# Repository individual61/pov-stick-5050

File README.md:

# POV-Stick

POV Stick 5050: A persistence of vision stick with 10 APA102C RGB LEDs, one button, and a surprise.

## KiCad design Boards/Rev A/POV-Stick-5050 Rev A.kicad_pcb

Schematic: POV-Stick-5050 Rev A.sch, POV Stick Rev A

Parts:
C1, C3: 0.1uF; C_0603_HandSoldering; Voltage Rating 50V; MFR P/N 06035C104KAZ2A
C2: 100uF; CP_Tantalum_Case-C_EIA-6032-28_Reflow; Voltage Rating 10V; MFR P/N TAJC107K010RNJ
C4: 10uF; C_0805_HandSoldering; Voltage Rating 16V; MFR P/N GRM21BR61C106KE15L
D1: Heartbeat LED; LED_0603_HandSoldering; MFR P/N LS L29K-G1J2-1-Z
J1: ISP_Header; ISP_Header_Pogo_2x03_Pitch2.54mm
J2: Batt Conn; JST_PH_S2B-PH-K_02x2.00mm_Angled; Part Number S2B-PH-K-S
R1: 4.7k; R_0603_HandSoldering; MFR P/N CR0603-FX-4701ELF
R2: 10k; R_0603_HandSoldering; MFR P/N RC0603FR-0710KL
R3: 1.5k; R_0603_HandSoldering; MFR P/N RC0603FR-071K5L
S1: Button; SW_TH_Tactile_Omron_B3F-10xx; Part Number B3F-1000
SW1: Power Switch; E-Switch_EG1390; Part Number AYZ0202AGRLC
U1: ATTINY85-20SU; SOIC-8_3.9x4.9mm_Pitch1.27mm
U2, U3, U4, U5, U6, U7, U8, U9, U10, U11: APA102C; LED_RGB_5050-6_Compact

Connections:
+BATT: C2.1, C3.1, C4.1, J1.2, R1.1, R2.1, SW1.2, SW1.5, U1.8 (VCC), U2.4, U3.4, U4.4, U5.4, U6.4, U7.4, U8.4, U9.4, U10.4, U11.4
/MOSI/WS2812Data: J1.4, U1.5 (PB0(MOSI/DI/SDA/AIN0/OC0A/~OC1A~/AREF/P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), U2.1
/PIN3/SW3: R2.2, S1.1, S1.2, U1.3 (PB4(XTAL2/CLKO/OC1B/ADC2/PCINT4))
/PIN6/SCK: J1.1, U1.6 (PB1(MISO/DO/AIN1/OC0B/OC1A/PCINT1))
/SCK/WS2812Clock: J1.3, U1.7 (PB2(SCK/USCK/SCL/T0/INT0/ADC1/PCINT2)), U2.2
GND: C1.2, C2.2, C3.2, C4.2, J1.6, J2.2, R3.2, S1.3, S1.4, U1.4 (GND), U2.3, U3.3, U4.3, U5.3, U6.3, U7.3, U8.3, U9.3, U10.3, U11.3
unnamed: C1.1, J1.5, R1.2, U1.1 (PB5(~RESET~/dW/ADC0/PCINT5))
unnamed: D1.1, R3.1
unnamed: D1.2, U1.2 (PB3(XTAL1/CLKI/~OC1B~/ADC3/PCINT3))
unnamed: J2.1, SW1.1, SW1.4
unnamed: U2.5, U3.2
unnamed: U2.6, U3.1
unnamed: U3.5, U4.2
unnamed: U3.6, U4.1
unnamed: U4.5, U5.2
unnamed: U4.6, U5.1
unnamed: U5.5, U6.2
unnamed: U5.6, U6.1
unnamed: U6.5, U7.2
unnamed: U6.6, U7.1
unnamed: U7.5, U8.2
unnamed: U7.6, U8.1
unnamed: U8.5, U9.2
unnamed: U8.6, U9.1
unnamed: U9.6, U10.1
unnamed: U9.5, U10.2
unnamed: U10.5, U11.2
unnamed: U10.6, U11.1

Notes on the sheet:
NOTE: TURN SWITCH OFF TO PROGRAM WITH ISP
ATTINY85 SOIC-8
Vf = 1.8V, 2 mA Ityp 5V-1.8 = 3.2V 3.2V/1.5k = 2.1 mA

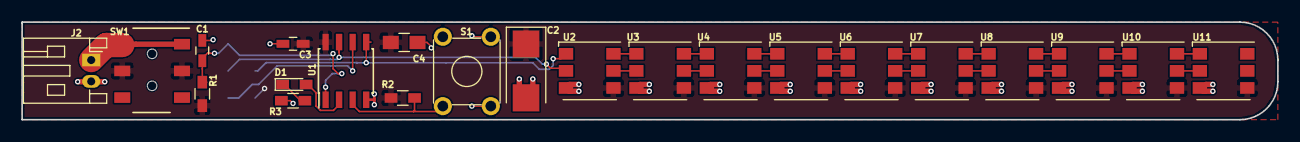
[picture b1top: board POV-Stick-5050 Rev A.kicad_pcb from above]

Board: 2 copper layers, 117.7 x 9.1 mm, 23 parts (1 on the bottom side), 28 nets.

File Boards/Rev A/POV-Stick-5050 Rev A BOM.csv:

"Id";"Designator";"Package";"Quantity";"Designation";"Supplier and ref";
1;"U1";"SOIC-8_3.9x4.9mm_Pitch1.27mm";1;"ATTINY85-20SU";;;
2;"C1,C3";"C_0603_HandSoldering";2;"0.1uF";;;
3;"C4";"C_0805_HandSoldering";1;"10uF";;;
4;"D1";"LED_0603_HandSoldering";1;"Heartbeat LED";;;
5;"J2";"JST_PH_S2B-PH-K_02x2.00mm_Angled";1;"Batt Conn";;;
6;"R1";"R_0603_HandSoldering";1;"4.7k";;;
7;"R2";"R_0603_HandSoldering";1;"10k";;;
8;"R3";"R_0603_HandSoldering";1;"1.5k";;;
9;"S1";"SW_TH_Tactile_Omron_B3F-10xx";1;"Button";;;
10;"SW1";"E-Switch_EG1390";1;"Power Switch";;;
11;"U2,U3,U4,U5,U6,U7,U8,U9,U10,U11";"LED_RGB_5050-6_Compact";10;"APA102C";;;
12;"C2";"CP_Tantalum_Case-C_EIA-6032-28_Reflow";1;"100uF";;;
13;"J1";"ISP_Header_Pogo_2x03_Pitch2.54mm";1;"ISP_Header";;;
14;"G***";"flamingo_logo_8-8_6-7";1;"LOGO";;;

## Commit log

2018-05-11 Created compact 5050 footprint
    And I'll have to create other smaller footprints or select smaller components if I want this stick thing to look nice.
2018-05-12 OSHPark settings, preliminary component locations
2018-05-12 Wired all non-power, added GND vias, prelim edge cut
2018-05-14 Finished layout
    Need to add Flamingo logo
2018-05-14 Final commit, as sent to OSHpark
2018-05-21 Starting code
    The AtTiny85's footprint is wrong, but I was able to bend the legs and make it work--again.
2018-05-21 First test code
    Board works! Testing heartbeat LED, button and APA102Cs. Success!
2018-05-21 Added text "wrong footprint" for aTtINY85
2018-05-23 Got 16 MHz working, fixed button pin number
2018-05-23 Two programs: rainbow and sweep
2018-05-23 Added BW heart bitmap
2018-05-24 Rainbow button up, rainbow zig zag button down
2018-05-24 Troubleshooting why heart wont show
2018-05-24 Heart is rotated 90 and has an edge
2018-05-24 First successful heart, not understanding indices.
2018-05-25 Changed to PROGMEM and 2D array
    Because screw trying to figure out the damn indices
2018-05-25 Viable: Rainbow/ Click for hear, separated.
2018-05-25 Ditched penis, now solid rainbow heart on button
2018-05-25 Stick #2: Solid hearts on button, slow rainbow button up.
2018-05-25 Candidate for final Stick#2
    20 mA button up
    60 mA button down
2018-05-25 Red heart, white border
2018-05-25 Final candidate: Pink heart white border
    20/60 mA
2018-05-25 Tyler Durden button implemented!!
2020-09-20 Tidying up
2020-09-24 Ok this is definitely the better program
2020-09-24 Added description to main.cpp
2020-09-24 Added stick 1's files to src subdir in preparation for merge to main
2020-09-24 Added parameter header files for each stick, common header file
2020-09-25 Still trying to fix undefined reference to loop1()
2020-09-25 Gave up and put everything in one file. Compiles.
2020-09-25 Tidied up single-file code. Still compiles.
2020-09-25 Made section breaks more readable. Added info preamble, CC BY 4.0 license blurb
2020-09-25 More code tidying
2020-09-25 Can now do arbitrarily-wide image 1 and image 1 in Stick 1
2020-09-25 Updated board files to KiCAD 5, added spreadsheet converter
2020-09-26 Now with longer penis.
    To do: The button should queue up a penis, not immediately cut from heart to cock.
    Also it's worth checking how the debounce time relates to number of hearts drawn. If the button is held down this would determine how frequently it is shown.
2020-09-29 Stick 1: Tyler Durden button is functional. We have penis.
